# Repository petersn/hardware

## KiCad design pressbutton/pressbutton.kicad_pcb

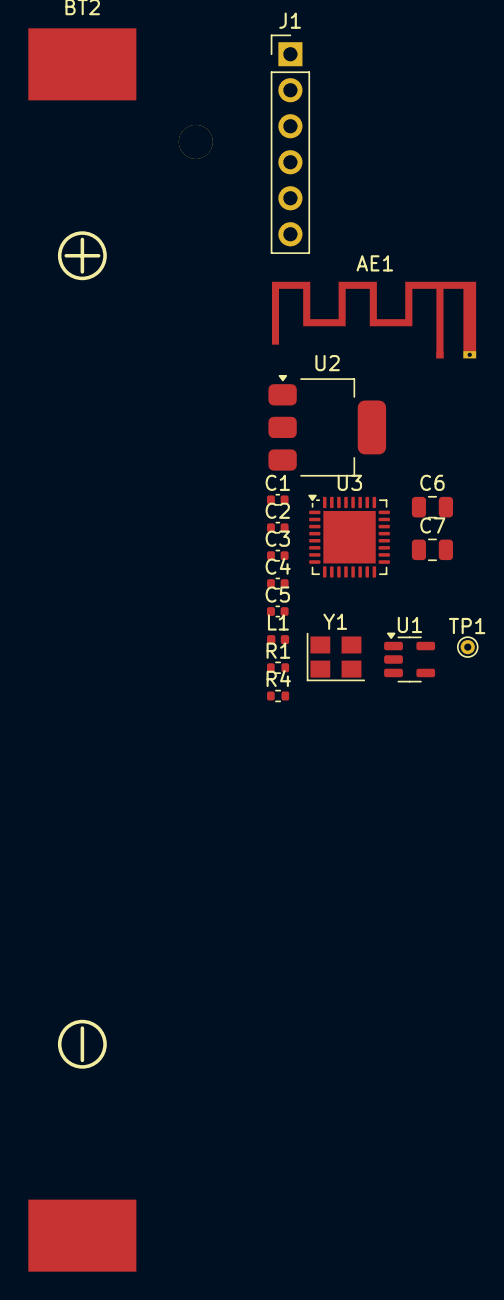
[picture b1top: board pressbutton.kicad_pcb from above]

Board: 2 copper layers, 18 parts (0 on the bottom side), 13 nets, no tracks yet.

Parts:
AE1: Texas_SWRA117D_2.4GHz_Left
BT2: BH-18650-B1BA002; BATTERY-SMD_18650-1S-L77.1-W20.7-1
C1, C2: 2.4p; C_0402_1005Metric
C3, C4: 15p; C_0402_1005Metric
C5: 10u; C_0402_1005Metric
C6, C7: 47u; C_0805_2012Metric
J1: Conn_01x06; PinHeader_1x06_P2.54mm_Vertical
L1: 1.8n; L_0402_1005Metric
R1: 1.27k; R_0402_1005Metric
R4: 470; R_0402_1005Metric
TP1: BATT; TestPoint_THTPad_D1.0mm_Drill0.5mm
U1: LTC4054ES5-4.2; TSOT-23-5
U2: NCP1117-3.3_SOT223; SOT-223-3_TabPin2
U3: ESP32-C3FH4; QFN-32-1EP_5x5mm_P0.5mm_EP3.7x3.7mm
Y1: ABM8-272-T3; Crystal_SMD_3225-4Pin_3.2x2.5mm

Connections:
+3V3: C5.1, C6.1, C7.1, J1.2, U2.2 (VO), U3.2 (VDD3P3), U3.3 (VDD3P3), U3.7 (CHIP_EN), U3.11 (VDD3P3_RTC), U3.17 (VDD3P3_CPU), U3.18 (VDD_SPI), U3.31 (VDDA), U3.32 (VDDA)
+BATT: BT2.2, TP1.1, U1.3 (BAT), U2.3 (VI)
/ANTENNA_IN: C1.1, L1.1, U3.1 (LNA_IN)
/BOOTSEL: J1.5, U3.15 (GPIO9)
/UART_RXD: J1.4, U3.27 (U0RXD)
/UART_TXD: J1.3, R4.2
/XTAL_N: C4.1, U3.29 (XTAL_N), Y1.3
/XTAL_P: C3.1, U3.30 (XTAL_P), Y1.1
GND: AE1.2, BT2.1, C1.2, C2.2, C3.2, C4.2, C5.2, C6.2, C7.2, J1.6, R1.2, U1.2 (GND), U2.1 (GND), U3.33 (GND), Y1.2, Y1.4
unnamed: AE1.1, C2.1, L1.2
unnamed: R1.1, U1.5 (PROG)
unnamed: R4.1, U3.28 (U0TXD)
VBUS: J1.1, U1.4 (V_{CC})

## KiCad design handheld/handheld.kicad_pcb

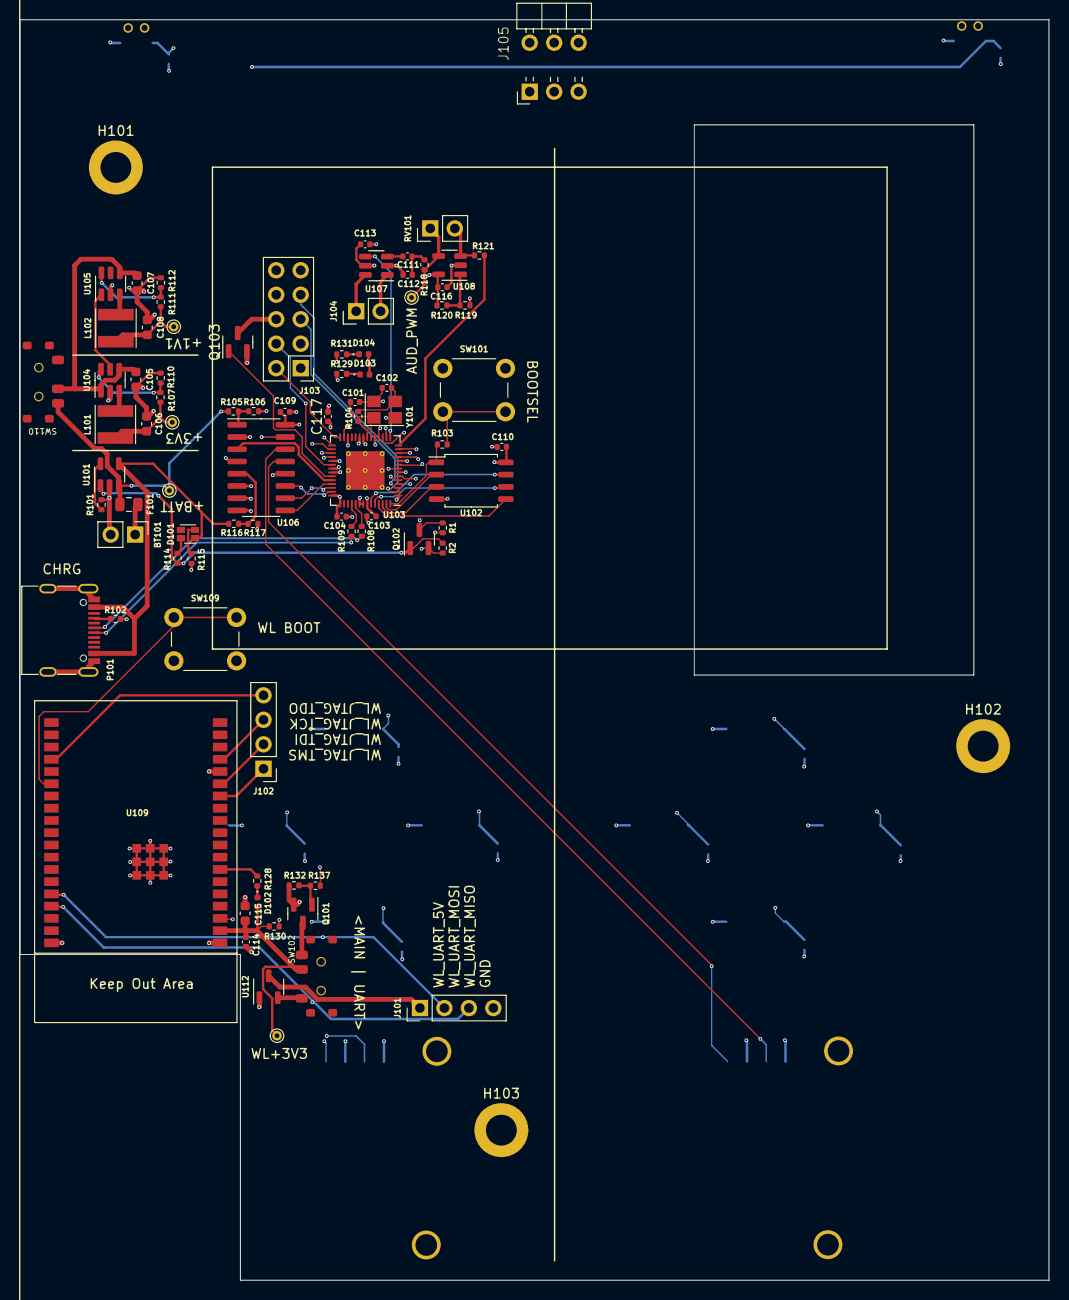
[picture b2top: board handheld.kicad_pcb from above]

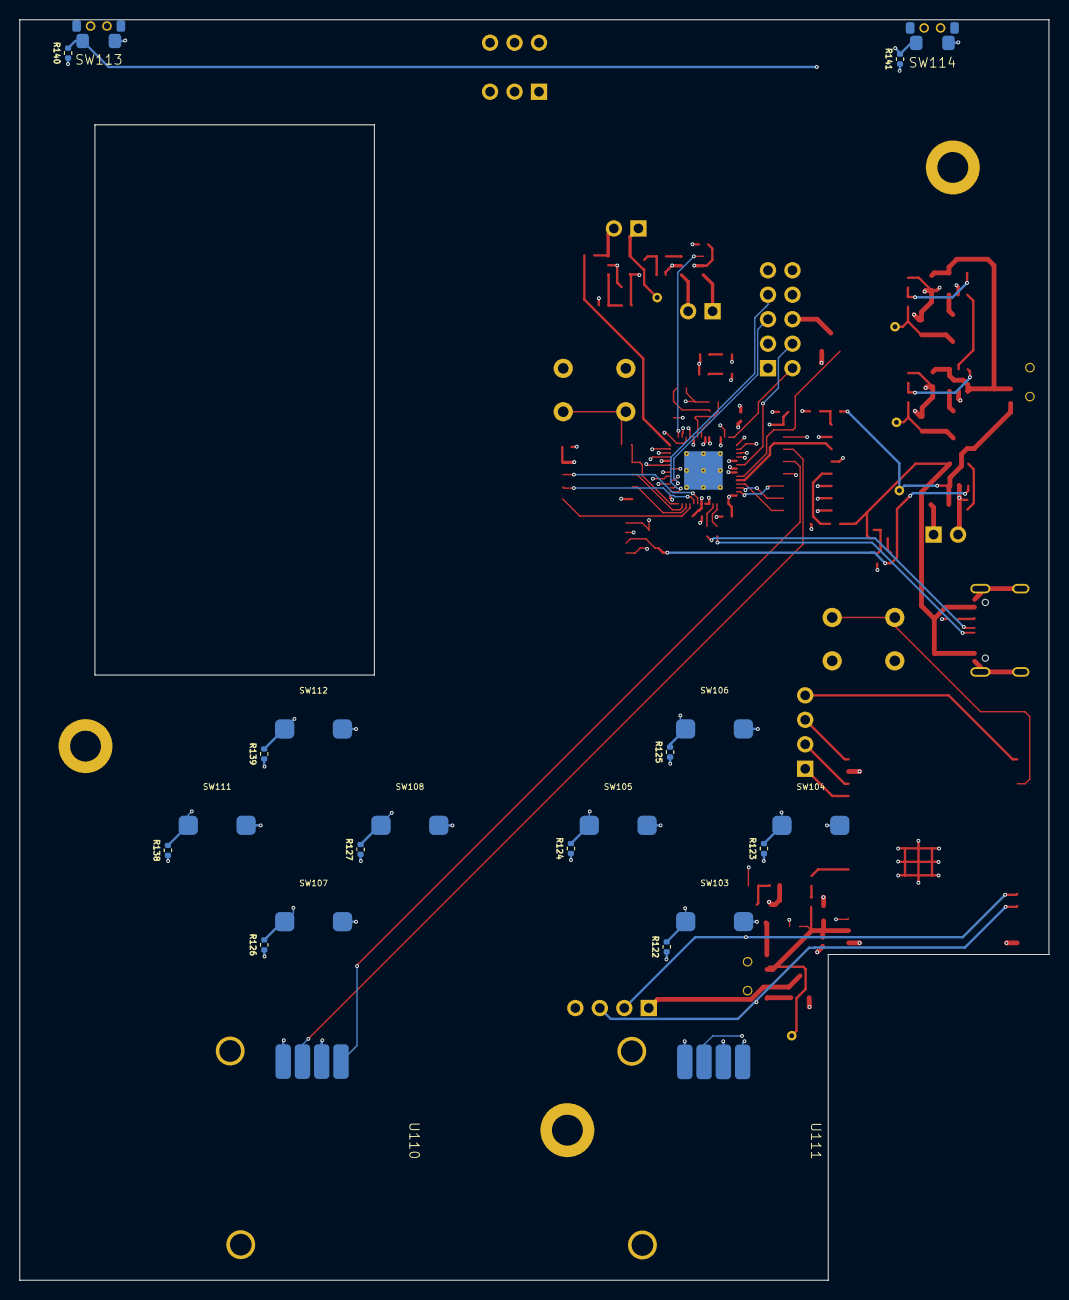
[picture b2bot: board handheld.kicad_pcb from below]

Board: 6 copper layers, 106.8 x 130.8 mm, 108 parts (22 on the bottom side), 91 nets.

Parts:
BT101: Battery_Cell; PinHeader_1x02_P2.54mm_Vertical
C101, C102: 15p; C_0402_1005Metric
C103, C104, C109, C110, C113, C116, C117: 1u; C_0402_1005Metric
C105, C107: 4.7u; C_0603_1608Metric
C106, C108: 10u; C_0603_1608Metric
C111, C114: 100n; C_0402_1005Metric
C112: 2.2n; C_0402_1005Metric
C115: 22u; C_0603_1608Metric
D101: LED_RBGA; LED_LiteOn_LTST-C19HE1WT
D102, D103, D104: LED; LED_0402_1005Metric
F101: I_{hold}=1A, I_{trip}=2A, R_{1max}=0.27Ω; Fuse_0805_2012Metric
H101, H102, H103: MountingHole_Pad; MountingHole_3.2mm_M3_DIN965_Pad
J101, J102: DNP; PinHeader_1x04_P2.54mm_Vertical
J103: Conn_02x05_Odd_Even; PinHeader_2x05_P2.54mm_Vertical
J104: Conn_01x02; PinHeader_1x02_P2.54mm_Vertical
J105: Conn_02x03_Odd_Even; 02x03_Edge_Board_Connector_ER06BGFBK
L101, L102: 2.2uH; L_Taiyo-Yuden_NR-40xx
P101: USB_C_Plug_USB2.0; USB_C_Receptacle_G-Switch_GT-USB-7010ASV
Q101, Q102, Q103: AO3401A; SOT-23
R1, R2, R105, R106, R116, R117, R119, R120, R122, R123, R124, R125, R126, R127, R130, R132, R138, R139, R140, R141: 47k; R_0402_1005Metric
R101: 1.27k; R_0402_1005Metric
R102: 5.1k; R_0402_1005Metric
R103, R104: 1k; R_0402_1005Metric
R107: 68k; R_0402_1005Metric
R108, R109: 27; R_0402_1005Metric
R110: 15k; R_0402_1005Metric
R111: 100k; R_0402_1005Metric
R112: 120k; R_0402_1005Metric
R114, R115, R137: 470; R_0402_1005Metric
R118: 2.2k; R_0402_1005Metric
R121: 10k; R_0402_1005Metric
R128, R129, R131: 220; R_0402_1005Metric
RV101: R_Potentiometer; PinHeader_1x02_P2.54mm_Vertical
SW101, SW109: SW_Omron_B3FS; SW_PUSH_6mm
SW102, SW110: SW_SPDT; MK-12C02-G025_Slide_Switch
SW103, SW104, SW105, SW106, SW107, SW108, SW111, SW112: SW_Push; ALPSALPINE_SKPMBHE010
SW113, SW114: SW_Push; Horizontal_Button_TS24CA
TP101: 3.3v; TestPoint_THTPad_D1.0mm_Drill0.5mm
TP102: 1.1v; TestPoint_THTPad_D1.0mm_Drill0.5mm
TP103: BATT; TestPoint_THTPad_D1.0mm_Drill0.5mm
TP104: AUDIO_PWM; TestPoint_THTPad_D1.0mm_Drill0.5mm
TP105: ESP32-3.3v; TestPoint_THTPad_D1.0mm_Drill0.5mm
U101: LTC4054ES5-4.2; TSOT-23-5
U102: W25Q128JVS; SOIC-8_5.23x5.23mm_P1.27mm
U103: RP2040; QFN-56-1EP_7x7mm_P0.4mm_EP4x4mm_ThermalVias
U104, U105: TLV62568DDC; SOT-23-6
U106: 4051; SOP-16_3.9x9.9mm_P1.27mm
U107: PAM8301; SOT-23-6
U108: LM321; SOT-23-5
U109: ESP32-WROVER-E; ESP32-WROVER-IE
U110, U111: 10k Pot Joystick; Flat_Analog_Stick
U112: XC6206PxxxMR; SOT-23-3
Y101: ABM8-272-T3; Crystal_SMD_3225-4Pin_3.2x2.5mm

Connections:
+1V1: C103.1, C108.1, C117.1, L102.2, R111.2, TP102.1, U103.23 (DVDD), U103.50 (DVDD)
+3V3: C104.1, C106.1, C109.1, C110.1, C113.1, C116.1, D103.2 (A), D104.2 (A), J103.8, J105.2, L101.2, Q101.2 (S), Q102.2 (S), Q103.2 (S), R2.1, R107.2, R120.1, R132.2, SW103.2, SW104.2, SW105.2, SW106.2, SW107.2, SW108.2, SW111.2, SW112.2, SW113.2, SW114.2, TP101.1, U102.8 (VCC), U103.1 (IOVDD), U103.10 (IOVDD), U103.22 (IOVDD), U103.26 (RUN), U103.33 (IOVDD), U103.42 (IOVDD), U103.43 (ADC_AVDD), U103.48 (USB_VDD), U103.49 (IOVDD), U106.16 (VDD), U107.5 (VDD), U108.5 (V+), U110.4 (PWR), U111.4 (PWR)
+3V8: C105.1, C107.1, SW110.2 (B), U104.1 (EN), U104.4 (VIN), U105.4 (VIN)
+BATT: F101.2, R105.1, SW110.1 (A), TP103.1, U101.3 (BAT)
/3V3_GOOD: U104.5 (PG), U105.1 (EN)
/ADC_MUX_S0: U103.39 (GPIO27_ADC1), U106.9 (C)
/ADC_MUX_S1: U103.40 (GPIO28_ADC2), U106.10 (B)
/ADC_MUX_S2: U103.41 (GPIO29_ADC3), U106.11 (A)
/AUDIO_EN: U103.15 (GPIO12), U107.4 (~SD)
/AUDIO_OUT: R121.2, U103.14 (GPIO11)
/BATT_SENSE: R105.2, R106.1, U106.1 (X4)
/BUTTON0: R122.2, SW103.1, U103.7 (GPIO5)
/BUTTON1: R123.2, SW104.1, U103.8 (GPIO6)
/BUTTON2: R124.2, SW105.1, U103.9 (GPIO7)
/BUTTON3: R125.2, SW106.1, U103.11 (GPIO8)
/BUTTON4: R126.2, SW107.1, U103.12 (GPIO9)
/BUTTON5: R127.2, SW108.1, U103.13 (GPIO10)
/BUTTON6: R138.2, SW111.1, U103.16 (GPIO13)
/BUTTON7: R139.2, SW112.1, U103.17 (GPIO14)
/BUTTON8: R140.2, SW113.1, U106.2 (X6)
/BUTTON9: R141.2, SW114.1, U106.4 (X7)
/DBG_LED0: R129.2, U103.35 (GPIO23)
/DBG_LED1: R131.2, U103.36 (GPIO24)
/GAME_CART_RX: J105.1, U103.27 (GPIO16)
/GAME_CART_TX: J105.3, U103.18 (GPIO15)
/GATED_WL_POWER: Q101.3 (D), SW102.1 (A)
/LCD_DC: J103.2, U103.28 (GPIO17)
/LCD_LED: Q103.1 (G), U103.37 (GPIO25)
/LCD_RESET: J103.4, U103.34 (GPIO22)
/LCD_SPI_CLK: J103.3, U103.4 (GPIO2)
/LCD_SPI_CS: J103.5, U103.3 (GPIO1)
/LCD_SPI_MISO: J103.7, U103.2 (GPIO0)
/LCD_SPI_MOSI: J103.1, U103.5 (GPIO3)
/MUXED_ADC: U103.38 (GPIO26_ADC0), U106.3 (X)
/QSPI_SCLK: U102.6 (CLK), U103.52 (QSPI_SCLK)
/QSPI_SD0: U102.5 (DI(IO0)), U103.53 (QSPI_SD0)
/QSPI_SD1: U102.2 (DO(IO1)), U103.55 (QSPI_SD1)
/QSPI_SD2: U102.3 (IO2), U103.54 (QSPI_SD2)
/QSPI_SD3: U102.7 (IO3), U103.51 (QSPI_SD3)
/QSPI_SS: R103.1, U102.1 (~CS), U103.56 (QSPI_SS)
/SPEAKER+: J104.1, U107.6 (OUT+)
/SPEAKER-: J104.2, U107.1 (OUT-)
/STICK0_X: U106.13 (X0), U110.1 (LeftRight)
/STICK0_Y: U106.14 (X1), U110.3 (UpDown)
/STICK1_X: U106.15 (X2), U111.1 (LeftRight)
/STICK1_Y: U106.12 (X3), U111.3 (UpDown)
/USB_D+: P101.A6 (D+), R108.2
/USB_D-: P101.A7 (D-), R109.2
/VBUS_SENSE: R116.2, R117.1, U106.5 (X5)
/WL_EN: R130.2, U103.30 (GPIO19), U109.3 (EN)
/WL_JTAG_TCK: J102.3, U109.16 (IO13)
/WL_JTAG_TDI: J102.2, U109.14 (IO12)
/WL_JTAG_TDO: J102.4, U109.23 (IO15)
/WL_JTAG_TMS: J102.1, U109.13 (IO14)
/WL_POWER: C114.1, C115.1, D102.2 (A), R130.1, SW102.2 (B), TP105.1, U109.2 (3V3)
/WL_POWER_~EN: R137.2, U103.29 (GPIO18)
/WL_UART_5V: J101.1, U112.3 (VI)
/WL_UART_MISO: J101.3, U103.32 (GPIO21), U109.35 (TXD0)
/WL_UART_MOSI: J101.2, U103.31 (GPIO20), U109.34 (RXD0)
/XIN: C101.1, U103.20 (XIN), Y101.1
/XOUT: R104.1, U103.21 (XOUT)
/~CHRG: Q102.1 (G), R2.2, R114.2, U101.1 (~CHRG)
/~USB_BOOT: R103.2, SW101.2
GND: BT101.2 (-), C101.2, C102.2, C103.2, C104.2, C105.2, C106.2, C107.2, C108.2, C109.2, C110.2, C112.1, C113.2, C114.2, C115.2, C116.2, C117.2, H101.1, H102.1, H103.1, J101.4, J103.9, J103.10, J105.5, P101.A1 (GND), P101.A12 (GND), P101.B1 (GND), P101.B12 (GND), P101.S1 (SHIELD), R1.1, R101.2, R102.2, R106.2, R110.1, R112.1, R115.1, R117.2, R119.2, R122.1, R123.1, R124.1, R125.1, R126.1, R127.1, R138.1, R139.1, R140.1, R141.1, SW101.1, SW109.2, U101.2 (GND), U102.4 (GND), U103.19 (TESTEN), U103.57 (GND), U104.2 (GND), U105.2 (GND), U106.6 (Inh), U106.7 (VEE), U106.8 (VSS), U107.2 (GND), U108.2 (V-), U109.1 (GND), U109.15 (GND), U109.38 (GND), U109.39 (GND_BOTTOM), U110.2 (GND), U111.2 (GND), U112.1 (GND), Y101.2, Y101.4
unnamed: BT101.1 (+), F101.1
unnamed: C102.1, R104.2, Y101.3
unnamed: C111.1, C112.2, R118.1
unnamed: D101.3 (GK), R115.2
unnamed: D101.1 (RK), R114.1
unnamed: D102.1 (K), R128.1
unnamed: D103.1 (K), R129.1
unnamed: D104.1 (K), R131.1
unnamed: J103.6, Q103.3 (D)
unnamed: P101.A5 (CC), R102.1
unnamed: Q101.1 (G), R132.1, R137.1
unnamed: Q102.3 (D), R1.2, U103.6 (GPIO4)
unnamed: R118.2, RV101.1, TP104.1, U108.4
unnamed: SW102.3 (C), U112.2 (VO)
unnamed: R101.1, U101.5 (PROG)
unnamed: R109.1, U103.46 (USB_DM)
unnamed: R108.1, U103.47 (USB_DP)
unnamed: R107.1, R110.2, U104.6 (FB)
unnamed: L101.1, U104.3 (SW)
unnamed: R111.1, R112.2, U105.6 (FB)
unnamed: L102.1, U105.3 (SW)
unnamed: C111.2, U107.3 (IN)
unnamed: R119.1, R120.2, U108.1 (+)
unnamed: R121.1, RV101.2, U108.3 (-)
unnamed: SW109.1, U109.25 (IO0)
unnamed: R128.2, U109.7 (IO35)
VBUS: D101.4 (A), P101.A4 (VBUS), P101.A9 (VBUS), P101.B4 (VBUS), P101.B9 (VBUS), R116.1, U101.4 (V_{CC})

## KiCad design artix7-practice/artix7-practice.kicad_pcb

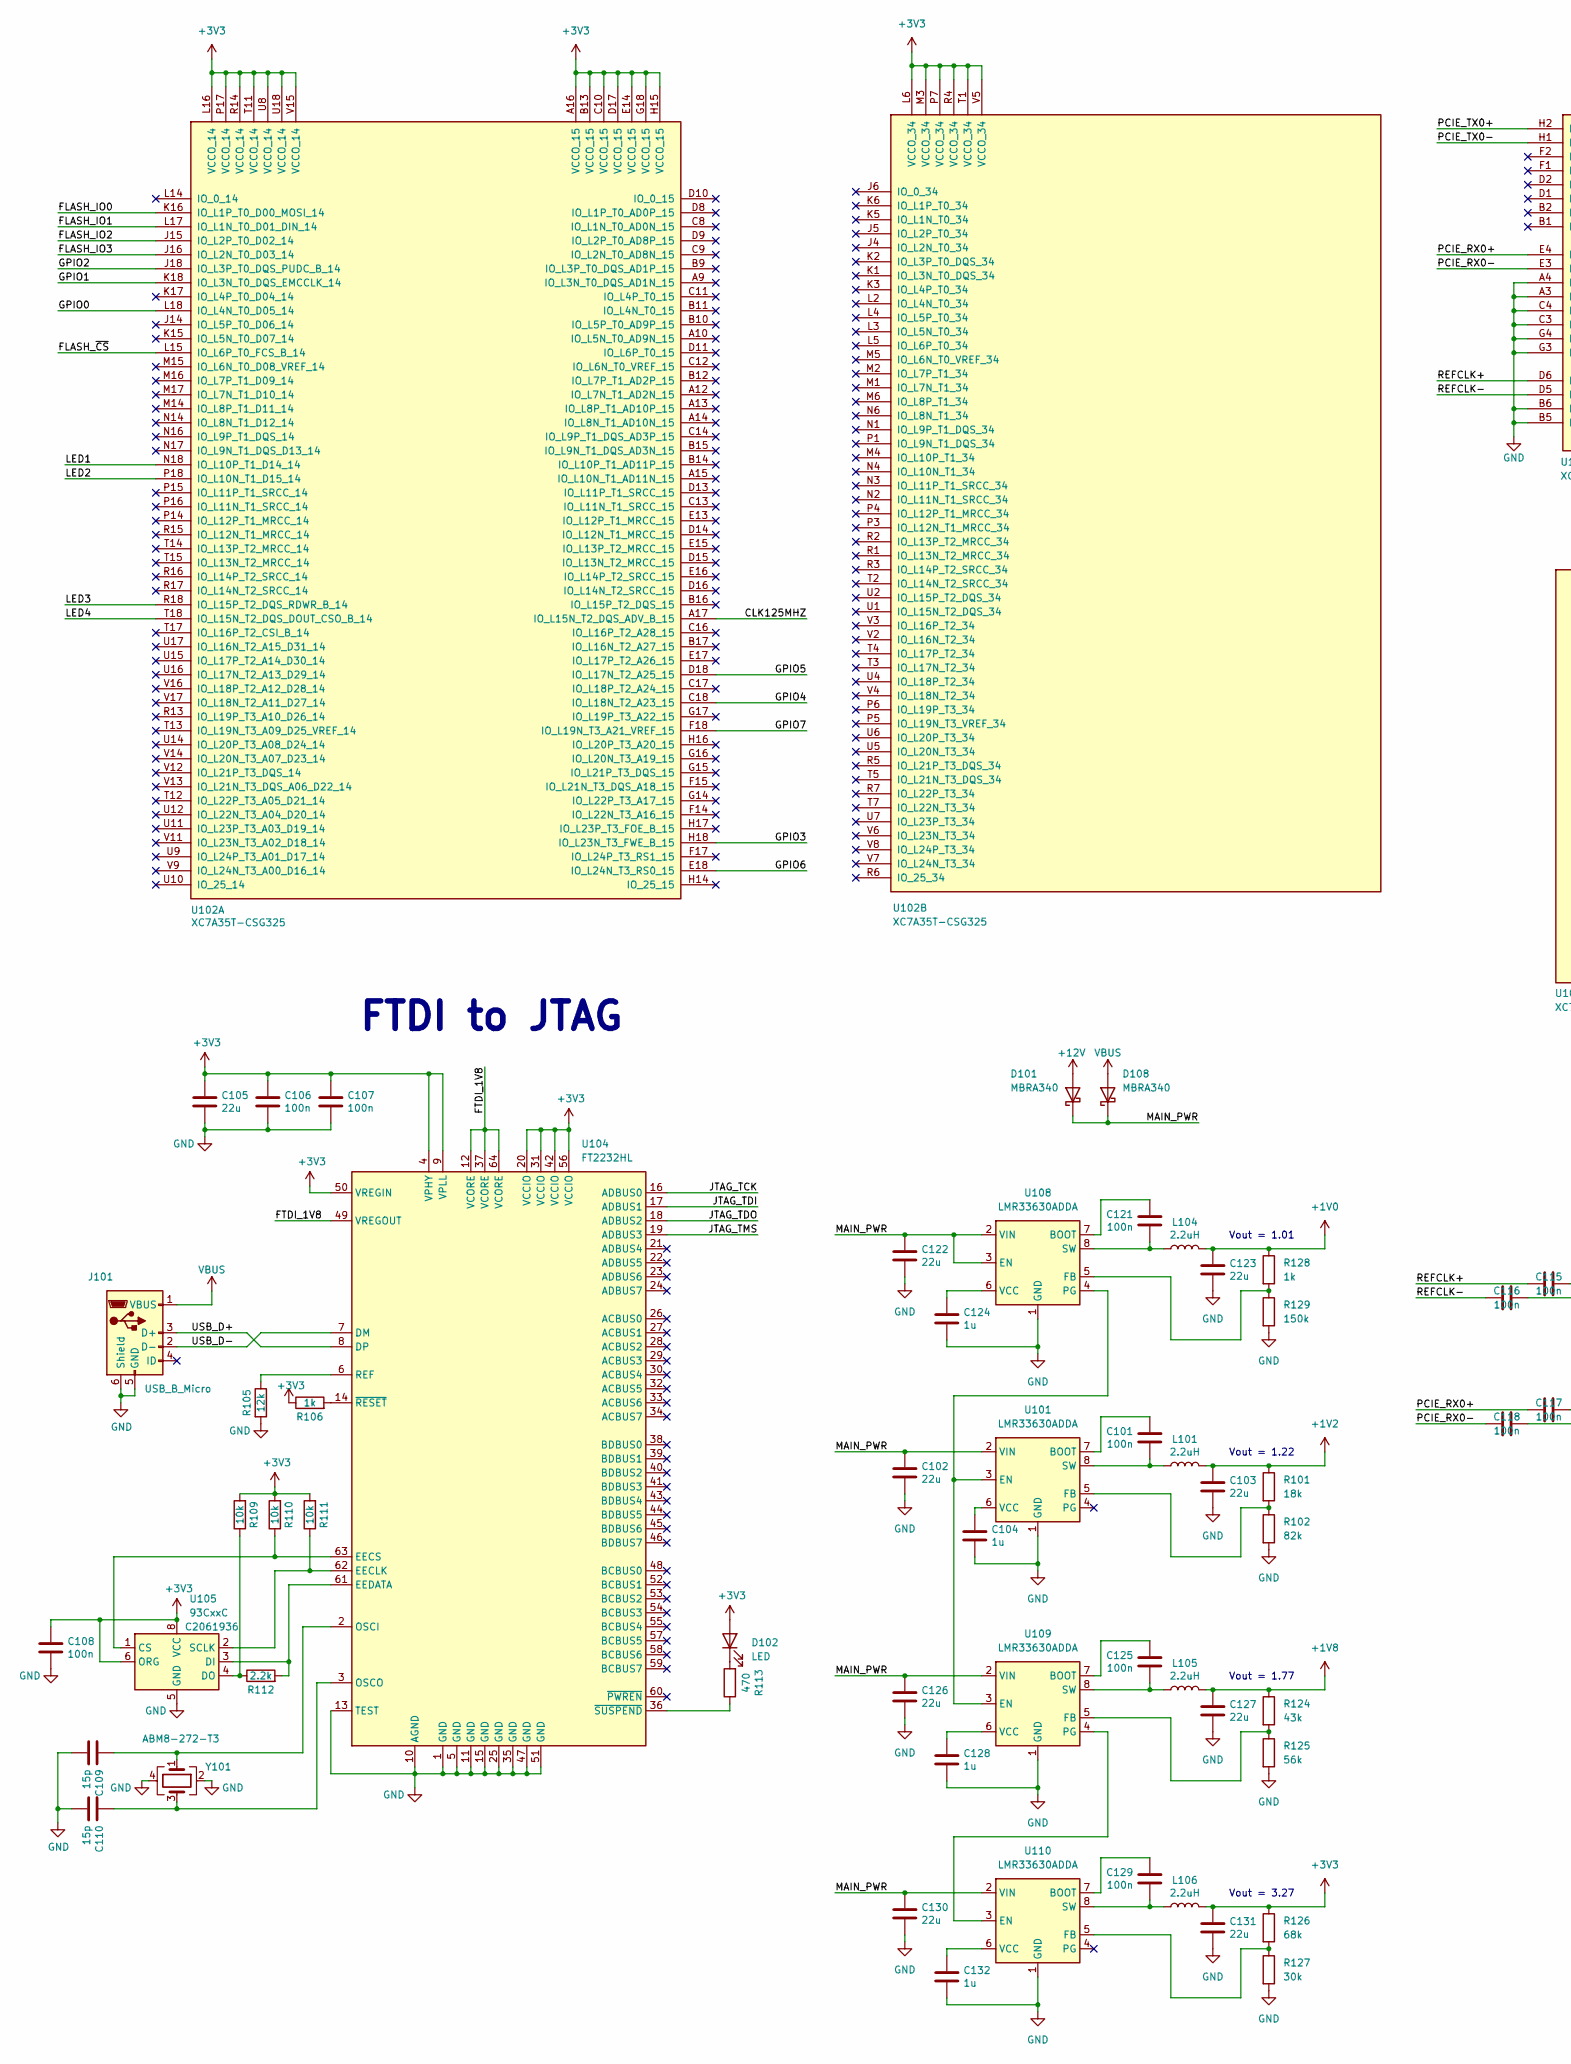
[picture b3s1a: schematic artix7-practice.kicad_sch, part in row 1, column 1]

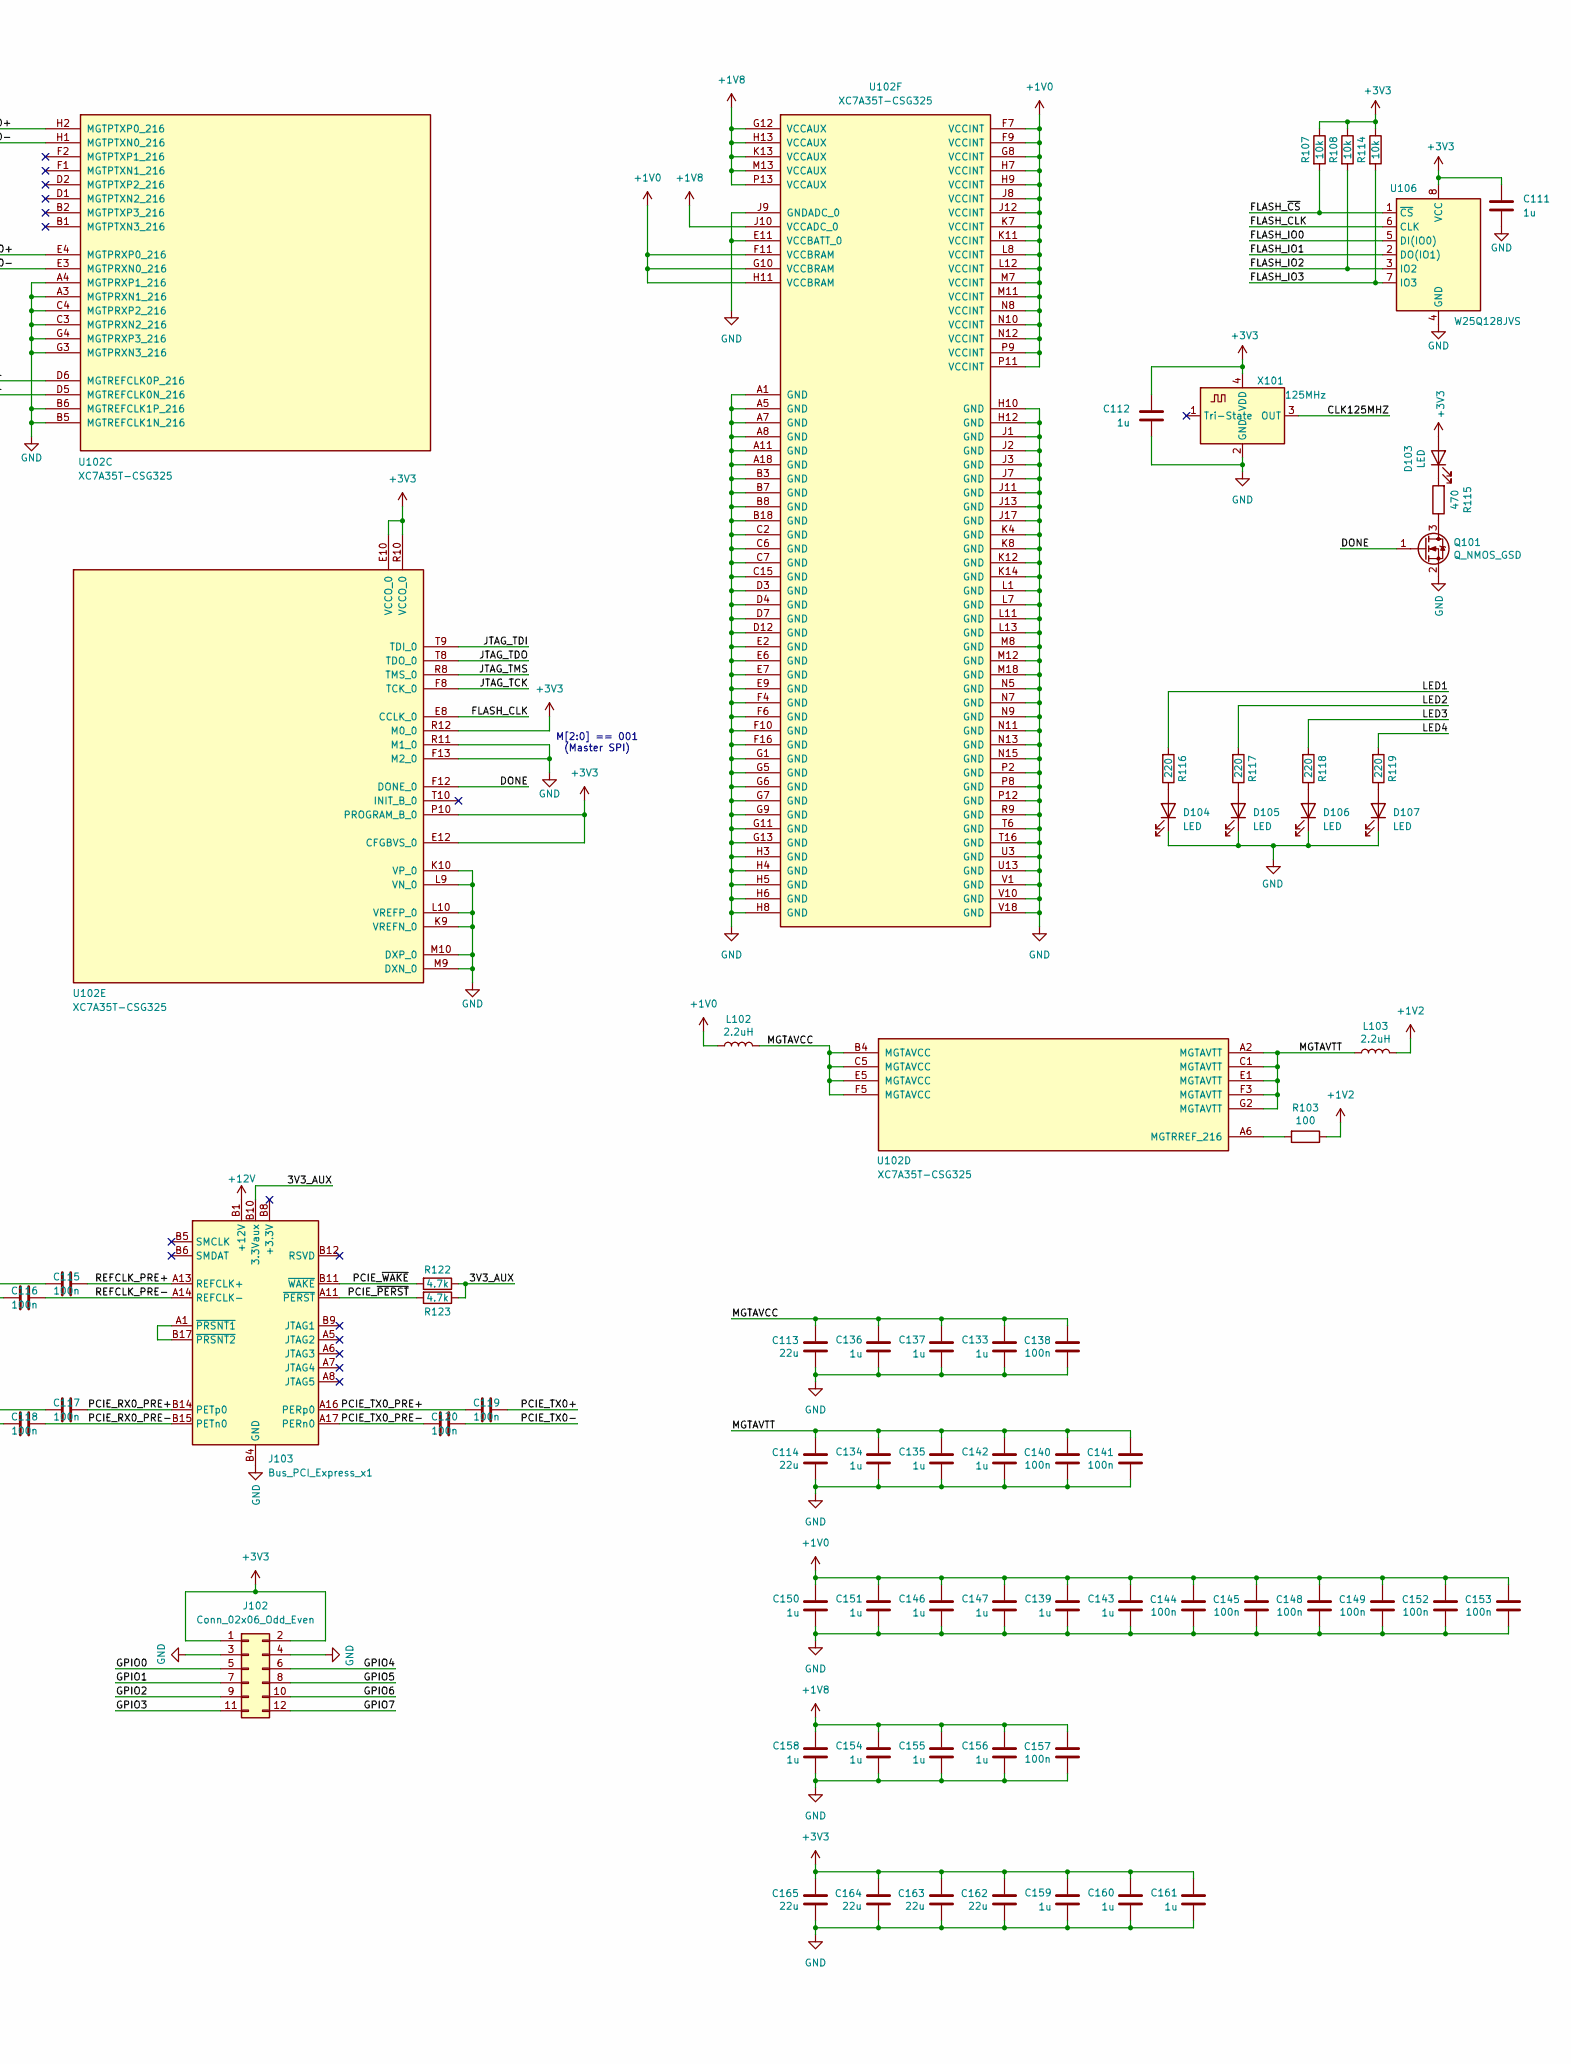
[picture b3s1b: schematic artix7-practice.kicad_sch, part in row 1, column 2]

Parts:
C101, C106, C107, C108, C121, C125, C129: 100n; C_0402_1005Metric; LCSC C1525
C102, C103, C122, C123, C126, C127, C130, C131: 22u; C_0805_2012Metric; LCSC C129303
C104, C111, C112, C124, C128, C132: 1u; C_0402_1005Metric; LCSC C14445
C105, C113, C114, C162, C163, C164, C165: 22u; C_0603_1608Metric; LCSC C59461
C109, C110: 15p; C_0402_1005Metric; LCSC C1548
C115, C116, C117, C118, C119, C120, C138, C140, C141, C144, C145, C148, C149, C152, C153, C157: 100n; C_0201_0603Metric; LCSC C76939
C133, C134, C135, C136, C137, C139, C142, C143, C146, C147, C150, C151, C154, C155, C156, C158, C159, C160, C161: 1u; C_0201_0603Metric; LCSC C87143
D101, D108: MBRA340; D_SMA; LCSC C26178
D102, D103, D104, D105, D106, D107: LED; LED_0402_1005Metric; LCSC C965790
J101: USB_B_Micro; USB_Micro-B_Amphenol_10103594-0001LF_Horizontal; LCSC C428495
J102: Conn_02x06_Odd_Even; PinSocket_2x06_P2.54mm_Vertical
J103: Bus_PCI_Express_x1; BUS_PCIexpress_x1
L101, L102, L103, L104, L105, L106: 2.2uH; L_Taiyo-Yuden_NR-40xx; LCSC C2929416
Q101: Q_NMOS_GSD; SOT-23; LCSC C8548
R101: 18k; R_0402_1005Metric; LCSC C25762
R102: 82k; R_0402_1005Metric; LCSC C4142
R103: 100; R_0402_1005Metric; LCSC C25076
R105: 12k; R_0402_1005Metric; LCSC C25752
R106, R128: 1k; R_0402_1005Metric; LCSC C11702
R107, R108, R109, R110, R111, R114: 10k; R_0402_1005Metric; LCSC C25744
R112: 2.2k; R_0402_1005Metric; LCSC C25879
R113, R115: 470; R_0402_1005Metric; LCSC C25117
R116, R117, R118, R119: 220; R_0402_1005Metric; LCSC C25151
R122, R123: 4.7k; R_0402_1005Metric; LCSC C25900
R124: 43k; R_0402_1005Metric; LCSC C8329
R125: 56k; R_0402_1005Metric; LCSC C25796
R126: 68k; R_0402_1005Metric; LCSC C36871
R127: 30k; R_0402_1005Metric; LCSC C25776
R129: 150k; R_0402_1005Metric; LCSC C25755
U101, U108, U109, U110: LMR33630ADDA; Texas_HSOP-8-1EP_3.9x4.9mm_P1.27mm_ThermalVias; LCSC C841384
U102: XC7A35T-CSG325; Xilinx_CSG325; LCSC C1521749
U104: FT2232HL; LQFP-64_10x10mm_P0.5mm; LCSC C27882
U105: 93CxxC; TSSOP-8_4.4x3mm_P0.65mm; LCSC C2061936
U106: W25Q128JVS; SOIC-8_5.23x5.23mm_P1.27mm; LCSC C97521
X101: 125MHz; Oscillator_SMD_7.0x5.0mm; LCSC C4353706
Y101: ABM8-272-T3; Crystal_SMD_3225-4Pin_3.2x2.5mm; LCSC C70565

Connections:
+1V0: C123.1, C139.1, C143.1, C144.1, C145.1, C146.1, C147.1, C148.1, C149.1, C150.1, C151.1, C152.1, C153.1, L102.1, L104.2, R128.1, U102.F7 (VCCINT), U102.F9 (VCCINT), U102.F11 (VCCBRAM), U102.G8 (VCCINT), U102.G10 (VCCBRAM), U102.H7 (VCCINT), U102.H9 (VCCINT), U102.H11 (VCCBRAM), U102.J8 (VCCINT), U102.J12 (VCCINT), U102.K7 (VCCINT), U102.K11 (VCCINT), U102.L8 (VCCINT), U102.L12 (VCCINT), U102.M7 (VCCINT), U102.M11 (VCCINT), U102.N8 (VCCINT), U102.N10 (VCCINT), U102.N12 (VCCINT), U102.P9 (VCCINT), U102.P11 (VCCINT)
+1V2: C103.1, L101.2, L103.2, R101.1, R103.1
+1V8: C127.1, C154.1, C155.1, C156.1, C157.1, C158.1, L105.2, R124.1, U102.G12 (VCCAUX), U102.H13 (VCCAUX), U102.J10 (VCCADC_0), U102.K13 (VCCAUX), U102.M13 (VCCAUX), U102.P13 (VCCAUX)
+3V3: C105.1, C106.1, C107.1, C108.1, C111.1, C112.1, C131.1, C159.1, C160.1, C161.1, C162.1, C163.1, C164.1, C165.1, D102.2 (A), D103.2 (A), J102.1, J102.2, L106.2, R106.1, R107.1, R108.1, R109.2, R110.2, R111.2, R114.1, R126.1, U102.A16 (VCCO_15), U102.B13 (VCCO_15), U102.C10 (VCCO_15), U102.D17 (VCCO_15), U102.E10 (VCCO_0), U102.E12 (CFGBVS_0), U102.E14 (VCCO_15), U102.G18 (VCCO_15), U102.H15 (VCCO_15), U102.L6 (VCCO_34), U102.L16 (VCCO_14), U102.M3 (VCCO_34), U102.P7 (VCCO_34), U102.P10 (PROGRAM_B_0), U102.P17 (VCCO_14), U102.R4 (VCCO_34), U102.R10 (VCCO_0), U102.R12 (M0_0), U102.R14 (VCCO_14), U102.T1 (VCCO_34), U102.T11 (VCCO_14), U102.U8 (VCCO_14), U102.U18 (VCCO_14), U102.V5 (VCCO_34), U102.V15 (VCCO_14), U104.4 (VPHY), U104.9 (VPLL), U104.20 (VCCIO), U104.31 (VCCIO), U104.42 (VCCIO), U104.50 (VREGIN), U104.56 (VCCIO), U105.6 (ORG), U105.8 (VCC), U106.8 (VCC), X101.4 (VDD)
+12V: D101.2 (A), J103.A2 (+12V), J103.A3 (+12V), J103.B1 (+12V), J103.B2 (+12V), J103.B3 (+12V)
/3V3_AUX: J103.B10 (3.3Vaux), R122.1, R123.1
/CLK125MHZ: U102.A17 (IO_L15N_T2_DQS_ADV_B_15), X101.3 (OUT)
/DONE: Q101.1 (G), U102.F12 (DONE_0)
/FLASH_CLK: U102.E8 (CCLK_0), U106.6 (CLK)
/FLASH_IO0: U102.K16 (IO_L1P_T0_D00_MOSI_14), U106.5 (DI(IO0))
/FLASH_IO1: U102.L17 (IO_L1N_T0_D01_DIN_14), U106.2 (DO(IO1))
/FLASH_IO2: R108.2, U102.J15 (IO_L2P_T0_D02_14), U106.3 (IO2)
/FLASH_IO3: R114.2, U102.J16 (IO_L2N_T0_D03_14), U106.7 (IO3)
/FLASH_~CS: R107.2, U102.L15 (IO_L6P_T0_FCS_B_14), U106.1 (~CS)
/FTDI_1V8: U104.12 (VCORE), U104.37 (VCORE), U104.49 (VREGOUT), U104.64 (VCORE)
/GPIO0: J102.5, U102.L18 (IO_L4N_T0_D05_14)
/GPIO1: J102.7, U102.K18 (IO_L3N_T0_DQS_EMCCLK_14)
/GPIO2: J102.9, U102.J18 (IO_L3P_T0_DQS_PUDC_B_14)
/GPIO3: J102.11, U102.H18 (IO_L23N_T3_FWE_B_15)
/GPIO4: J102.6, U102.C18 (IO_L18N_T2_A23_15)
/GPIO5: J102.8, U102.D18 (IO_L17N_T2_A25_15)
/GPIO6: J102.10, U102.E18 (IO_L24N_T3_RS0_15)
/GPIO7: J102.12, U102.F18 (IO_L19N_T3_A21_VREF_15)
/JTAG_TCK: U102.F8 (TCK_0), U104.16 (ADBUS0)
/JTAG_TDI: U102.T9 (TDI_0), U104.17 (ADBUS1)
/JTAG_TDO: U102.T8 (TDO_0), U104.18 (ADBUS2)
/JTAG_TMS: U102.R8 (TMS_0), U104.19 (ADBUS3)
/LED1: R116.2, U102.N18 (IO_L10P_T1_D14_14)
/LED2: R117.2, U102.P18 (IO_L10N_T1_D15_14)
/LED3: R118.2, U102.R18 (IO_L15P_T2_DQS_RDWR_B_14)
/LED4: R119.2, U102.T18 (IO_L15N_T2_DQS_DOUT_CSO_B_14)
/MAIN_PWR: C102.1, C122.1, C126.1, C130.1, D101.1 (K), D108.1 (K), U101.2 (VIN), U108.2 (VIN), U108.3 (EN), U109.2 (VIN), U110.2 (VIN)
/MGTAVCC: C113.1, C133.1, C136.1, C137.1, C138.1, L102.2, U102.B4 (MGTAVCC), U102.C5 (MGTAVCC), U102.E5 (MGTAVCC), U102.F5 (MGTAVCC)
/MGTAVTT: C114.1, C134.1, C135.1, C140.1, C141.1, C142.1, L103.1, U102.A2 (MGTAVTT), U102.C1 (MGTAVTT), U102.E1 (MGTAVTT), U102.F3 (MGTAVTT), U102.G2 (MGTAVTT)
/PCIE_RX0+: C117.1, U102.E4 (MGTPRXP0_216)
/PCIE_RX0-: C118.1, U102.E3 (MGTPRXN0_216)
/PCIE_RX0_PRE+: C117.2, J103.B14 (PETp0)
/PCIE_RX0_PRE-: C118.2, J103.B15 (PETn0)
/PCIE_TX0+: C119.2, U102.H2 (MGTPTXP0_216)
/PCIE_TX0-: C120.2, U102.H1 (MGTPTXN0_216)
/PCIE_TX0_PRE+: C119.1, J103.A16 (PERp0)
/PCIE_TX0_PRE-: C120.1, J103.A17 (PERn0)
/PCIE_~PERST: J103.A11 (~PERST), R123.2
/PCIE_~WAKE: J103.B11 (~WAKE), R122.2
/REFCLK+: C115.1, U102.D6 (MGTREFCLK0P_216)
/REFCLK-: C116.1, U102.D5 (MGTREFCLK0N_216)
/REFCLK_PRE+: C115.2, J103.A13 (REFCLK+)
/REFCLK_PRE-: C116.2, J103.A14 (REFCLK-)
/USB_D+: J101.3 (D+), U104.8 (DP)
/USB_D-: J101.2 (D-), U104.7 (DM)
GND: C102.2, C103.2, C104.2, C105.2, C106.2, C107.2, C108.2, C109.2, C110.2, C111.2, C112.2, C113.2, C114.2, C122.2, C123.2, C124.2, C126.2, C127.2, C128.2, C130.2, C131.2, C132.2, C133.2, C134.2, C135.2, C136.2, C137.2, C138.2, C139.2, C140.2, C141.2, C142.2, C143.2, C144.2, C145.2, C146.2, C147.2, C148.2, C149.2, C150.2, C151.2, C152.2, C153.2, C154.2, C155.2, C156.2, C157.2, C158.2, C159.2, C160.2, C161.2, C162.2, C163.2, C164.2, C165.2, D104.1 (K), D105.1 (K), D106.1 (K), D107.1 (K), J101.5 (GND), J101.6 (Shield), J102.3, J102.4, J103.A4 (GND), J103.A12 (GND), J103.A15 (GND), J103.A18 (GND), J103.B4 (GND), J103.B7 (GND), J103.B13 (GND), J103.B16 (GND), J103.B18 (GND), Q101.2 (S), R102.2, R105.2, R125.2, R127.2, R129.2, U101.1 (GND), U101.9 (GND), U102.A1 (GND), U102.A3 (MGTPRXN1_216), U102.A4 (MGTPRXP1_216), U102.A5 (GND), U102.A7 (GND), U102.A8 (GND), U102.A11 (GND), U102.A18 (GND), U102.B3 (GND), U102.B5 (MGTREFCLK1N_216), U102.B6 (MGTREFCLK1P_216), U102.B7 (GND), U102.B8 (GND), U102.B18 (GND), U102.C2 (GND), U102.C3 (MGTPRXN2_216), U102.C4 (MGTPRXP2_216), U102.C6 (GND), U102.C7 (GND), U102.C15 (GND), U102.D3 (GND), U102.D4 (GND), U102.D7 (GND), U102.D12 (GND), U102.E2 (GND), U102.E6 (GND), U102.E7 (GND), U102.E9 (GND), U102.E11 (VCCBATT_0), U102.F4 (GND), U102.F6 (GND), U102.F10 (GND), U102.F13 (M2_0), U102.F16 (GND), U102.G1 (GND), U102.G3 (MGTPRXN3_216), U102.G4 (MGTPRXP3_216), U102.G5 (GND), U102.G6 (GND), U102.G7 (GND), U102.G9 (GND), U102.G11 (GND), U102.G13 (GND), U102.H3 (GND), U102.H4 (GND), U102.H5 (GND), U102.H6 (GND), U102.H8 (GND), U102.H10 (GND), U102.H12 (GND), U102.J1 (GND), U102.J2 (GND), U102.J3 (GND), U102.J7 (GND), U102.J9 (GNDADC_0), U102.J11 (GND), U102.J13 (GND), U102.J17 (GND), U102.K4 (GND), U102.K8 (GND), U102.K9 (VREFN_0), U102.K10 (VP_0), U102.K12 (GND), U102.K14 (GND), U102.L1 (GND), U102.L7 (GND), U102.L9 (VN_0), U102.L10 (VREFP_0), U102.L11 (GND), U102.L13 (GND), U102.M8 (GND), U102.M9 (DXN_0), U102.M10 (DXP_0), U102.M12 (GND), U102.M18 (GND), U102.N5 (GND), U102.N7 (GND), U102.N9 (GND), U102.N11 (GND), U102.N13 (GND), U102.N15 (GND), U102.P2 (GND), U102.P8 (GND), U102.P12 (GND), U102.R9 (GND), U102.R11 (M1_0), U102.T6 (GND), U102.T16 (GND), U102.U3 (GND), U102.U13 (GND), U102.V1 (GND), U102.V10 (GND), U102.V18 (GND), U104.1 (GND), U104.5 (GND), U104.10 (AGND), U104.11 (GND), U104.13 (TEST), U104.15 (GND), U104.25 (GND), U104.35 (GND), U104.47 (GND), U104.51 (GND), U105.5 (GND), U106.4 (GND), U108.1 (GND), U108.9 (GND), U109.1 (GND), U109.9 (GND), U110.1 (GND), U110.9 (GND), X101.2 (GND), Y101.2, Y101.4
unnamed: D102.1 (K), R113.2
unnamed: D103.1 (K), R115.2
unnamed: D104.2 (A), R116.1
unnamed: D105.2 (A), R117.1
unnamed: D106.2 (A), R118.1
unnamed: D107.2 (A), R119.1
unnamed: J103.A1 (~PRSNT1), J103.B17 (~PRSNT2)
unnamed: Q101.3 (D), R115.1
unnamed: C101.1, U101.7 (BOOT)
unnamed: U101.3 (EN), U108.4 (PG), U109.3 (EN)
unnamed: R101.2, R102.1, U101.5 (FB)
unnamed: C101.2, L101.1, U101.8 (SW)
unnamed: C104.1, U101.6 (VCC)
unnamed: R103.2, U102.A6 (MGTRREF_216)
unnamed: R111.1, U104.62 (EECLK), U105.2 (SCLK)
unnamed: R110.1, U104.63 (EECS), U105.1 (CS)
unnamed: R112.2, U104.61 (EEDATA), U105.3 (DI)
unnamed: C109.1, U104.2 (OSCI), Y101.1
unnamed: C110.1, U104.3 (OSCO), Y101.3
unnamed: R105.1, U104.6 (REF)
unnamed: R106.2, U104.14 (~RESET)
unnamed: R113.1, U104.36 (~SUSPEND)
unnamed: R109.1, R112.1, U105.4 (DO)
unnamed: C121.1, U108.7 (BOOT)
unnamed: R128.2, R129.1, U108.5 (FB)
unnamed: C121.2, L104.1, U108.8 (SW)
unnamed: C124.1, U108.6 (VCC)
unnamed: C125.1, U109.7 (BOOT)
unnamed: R124.2, R125.1, U109.5 (FB)
unnamed: U109.4 (PG), U110.3 (EN)
unnamed: C125.2, L105.1, U109.8 (SW)
unnamed: C128.1, U109.6 (VCC)
unnamed: C129.1, U110.7 (BOOT)
unnamed: R126.2, R127.1, U110.5 (FB)
unnamed: C129.2, L106.1, U110.8 (SW)
unnamed: C132.1, U110.6 (VCC)
VBUS: D108.2 (A), J101.1 (VBUS)

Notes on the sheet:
Vout = 1.22
FTDI to JTAG
Vout = 1.01
M[2:0] == 001 (Master SPI)
Vout = 3.27
Vout = 1.77

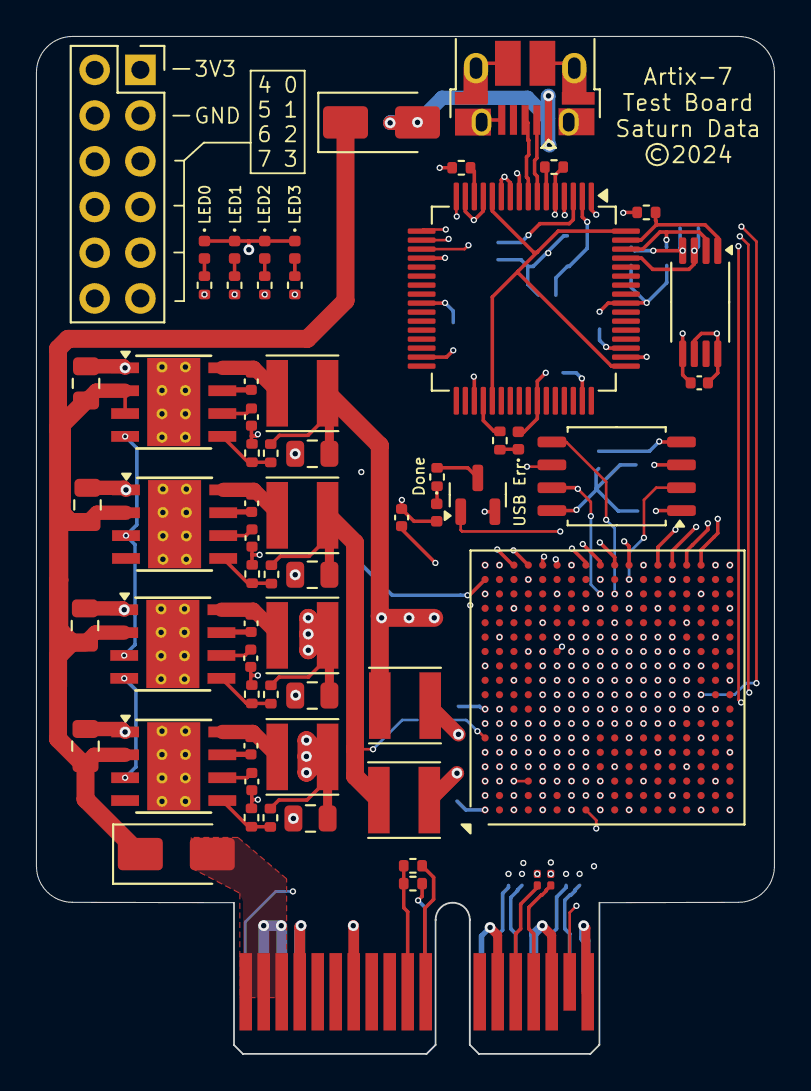
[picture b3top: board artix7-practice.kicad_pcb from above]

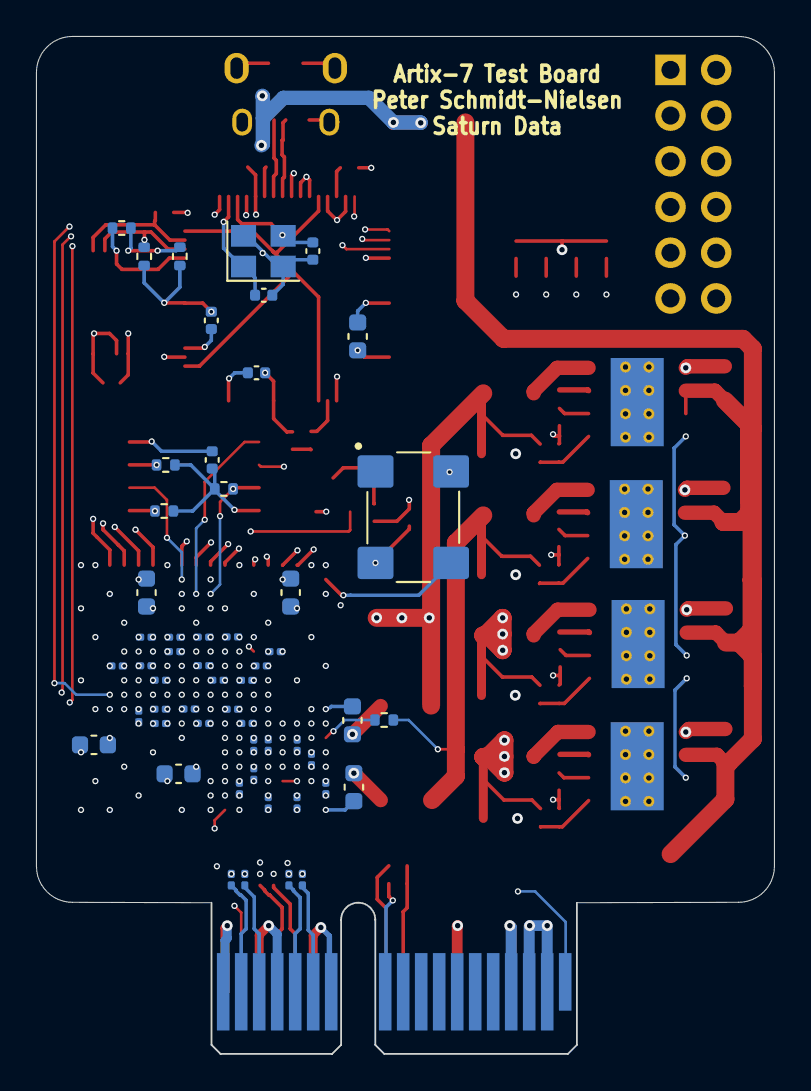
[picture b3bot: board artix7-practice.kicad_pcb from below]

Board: 8 copper layers, 41.0 x 56.5 mm, 119 parts (54 on the bottom side), 88 nets.

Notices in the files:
artix7-practice/artix7-practice.kicad_pcb:
©2024
